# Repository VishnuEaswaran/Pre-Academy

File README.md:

# Pre-Academy
Documentation of the Pre Academy done in Fab Lab Trivandrum.

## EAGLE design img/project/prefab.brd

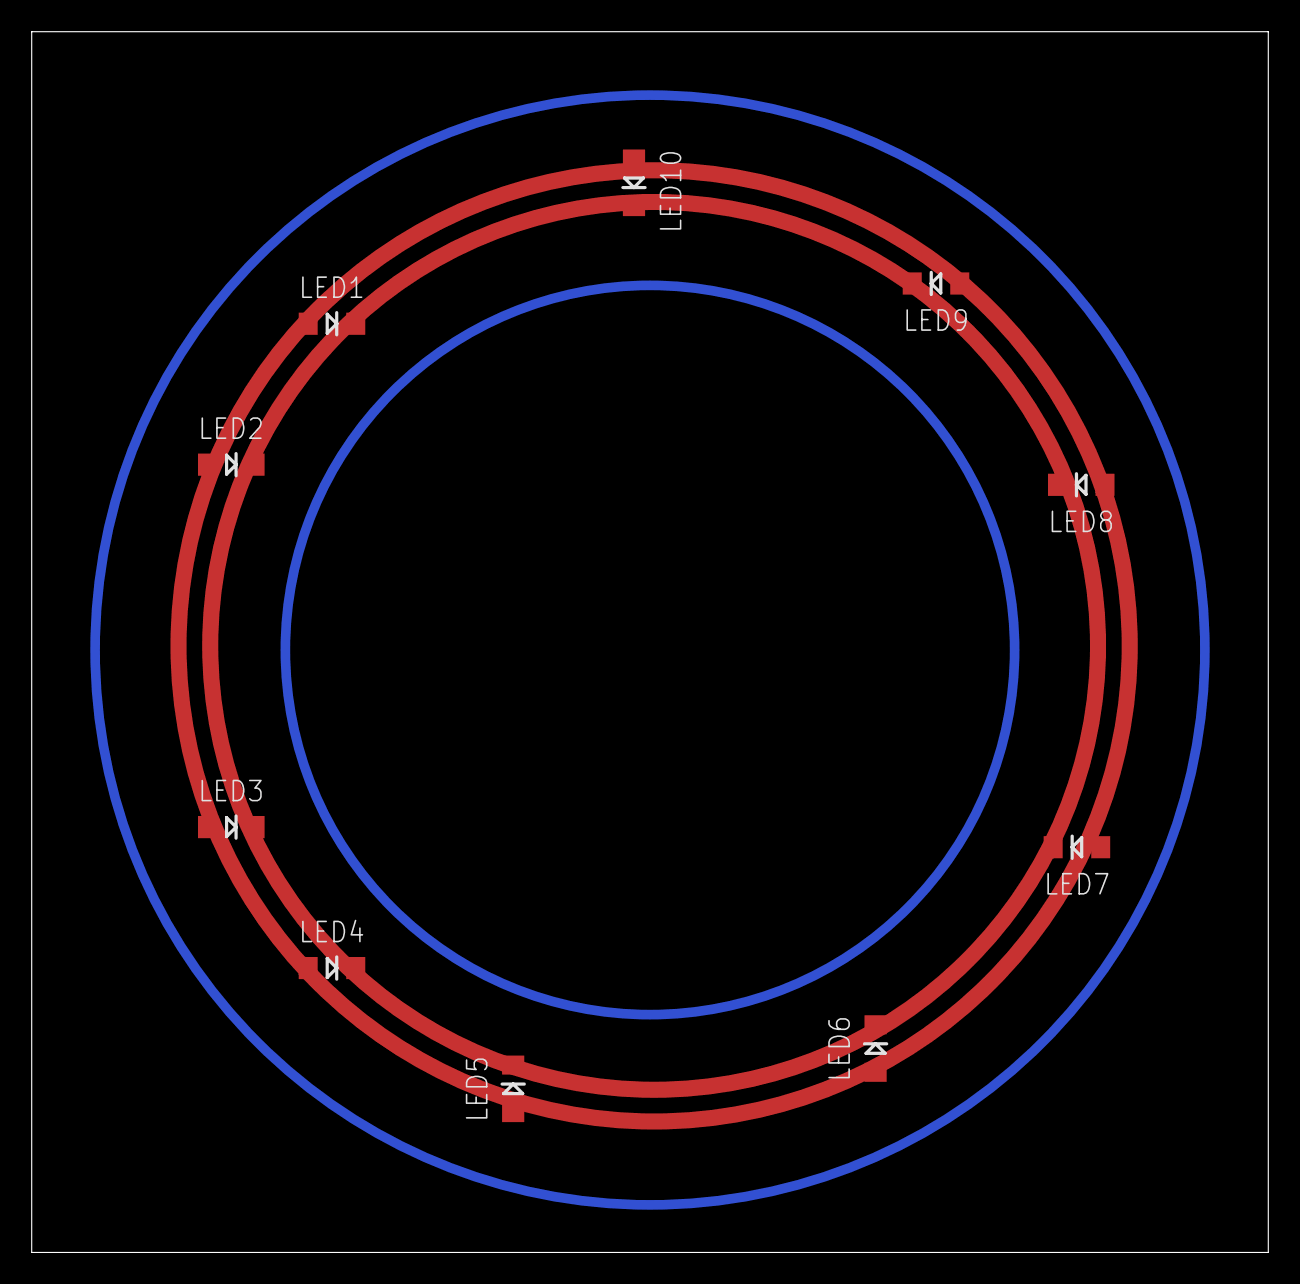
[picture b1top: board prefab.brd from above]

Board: 2 copper layers, 78.0 x 77.0 mm, 10 parts (0 on the bottom side), 2 nets, no tracks yet.

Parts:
LED1, LED2, LED3, LED4, LED5, LED6, LED7, LED8, LED9, LED10: LED-1206

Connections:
unnamed: LED1.A, LED2.A, LED3.A, LED4.A, LED5.A, LED6.A, LED7.A, LED8.A, LED9.A, LED10.A
unnamed: LED1.C, LED2.C, LED3.C, LED4.C, LED5.C, LED6.C, LED7.C, LED8.C, LED9.C, LED10.C

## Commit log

2017-02-24 Pre Acad doc shifted

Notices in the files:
parts and their libraries:
LilyPad-Wearables: Licensing:Creative Commons ShareAlike 4.0 International - https://creativecommons.org/licenses/by-sa/4.0
